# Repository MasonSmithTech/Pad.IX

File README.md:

# Pad.IX, a custom 9 key macropad

this project is a spot where the code, schematics, 3d models, and other files related to the Hack Club Stardance "HackPad" project are located, with my iteration named "Pad.IX" since it has nine keys. 

The Pad.IX is a nine key macro pad with an encoder and OLED screen, with future hopes of implementing VIA for custom keymapping.

## CAD
The case was modeled inside of OnShape (A new tool for me) and renders (as seen above) were created inside of fusion 360. The case features a top piece which holds the switches and pcb, and a bottom piece to protect the electronics, with the two parts being bolted together with M3 bolts and heat press inserts. 
The case was somewhat influenced by the OZO Keyboards Skeleton Keyboard Case, but mainly it is just an interesting looking open shell design that appeared in my brain on the bus home from school!

## PCB
the schematic and PCB are created using KiCad and LOTS of google.

schematic:

PCB:

## Firmware
This hackpad uses QMK firmware for everything.

the rotary encoder changes volume. press to mute
The 9 keys currently act as ma number pad
The OLED is a status display of sorts (mainly says "Pad.IX" tho)
Hopefully VIA support will be added once I actually build the thing irl

Thats pretty much it the firmware was pretty confusing to make so idk what to say

## Bill Of Materials 
    - 9x cherry MX switches
    - 9x DSA Keycaps (not required)
    - 1x 0.91" 128x32 OLED Display
    - 1x Seed XIAO RP2040
    - 1x EC11 Rotary Encoder
    - 1x Custom designed and manufactured pcb
    - 1x 3d printed top housing
    - 1x 3d printed bottom housing
    - 4x M3 heatpress inserts
    - 4x M3x16mm SHCS Bolts
    - 10x 1N4148 DO-35 Diodes

## Software
    - QMK MSYS
    - Fusion 360
    - KiCad 9.0    
    - Onshape
    - Visual Studio Code
    - File Explorer

## Author's Note
Thanks to the people at Hack Club this was an amazing experience! This is my first Hack Club build but I am looking forward to doing so much more in the future!
Also thanks to google cuz this was VERY confusing!

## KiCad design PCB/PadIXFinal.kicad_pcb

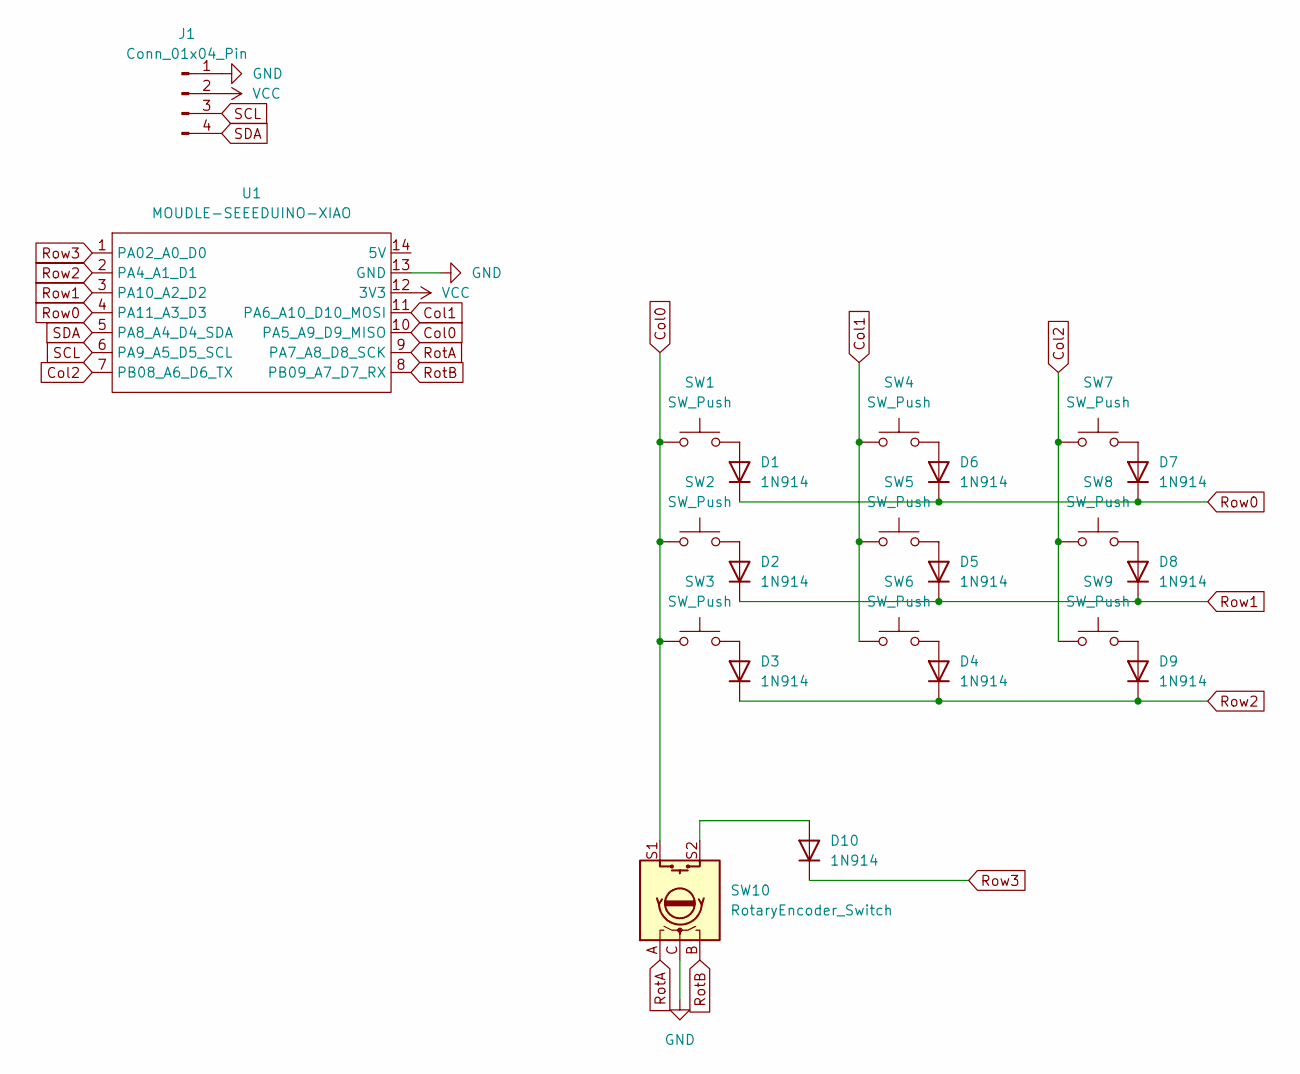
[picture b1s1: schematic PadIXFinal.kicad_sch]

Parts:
D1, D2, D3, D4, D5, D6, D7, D8, D9, D10: 1N914; D_DO-35_SOD27_P7.62mm_Horizontal
J1: Conn_01x04_Pin; PinHeader_1x04_P2.54mm_Vertical
SW1, SW2, SW3, SW4, SW5, SW6, SW7, SW8, SW9: SW_Push; SW_Cherry_MX_1.00u_PCB
SW10: RotaryEncoder_Switch; RotaryEncoder_Alps_EC11E-Switch_Vertical_H20mm
U1: MOUDLE-SEEEDUINO-XIAO; XIAO-Generic-Hybrid-14P-2.54-21X17.8MM

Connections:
Col1: SW4.1, SW5.1, SW6.1, U1.11 (PA6_A10_D10_MOSI)
Col2: SW7.1, SW8.1, SW9.1, U1.7 (PB08_A6_D6_TX)
GND: D10.2 (A), J1.1, SW10.C, SW10.S2, U1.13 (GND)
unnamed: D1.2 (A), SW1.2
unnamed: D2.2 (A), SW2.2
unnamed: D3.2 (A), SW3.2
unnamed: D4.2 (A), SW6.2
unnamed: D5.2 (A), SW5.2
unnamed: D6.2 (A), SW4.2
unnamed: D7.2 (A), SW7.2
unnamed: D8.2 (A), SW8.2
unnamed: D9.2 (A), SW9.2
RotA: SW10.A, U1.9 (PA7_A8_D8_SCK)
RotB: SW10.B, U1.8 (PB09_A7_D7_RX)
Row0: D1.1 (K), D6.1 (K), D7.1 (K), U1.4 (PA11_A3_D3)
Row1: D2.1 (K), D5.1 (K), D8.1 (K), U1.3 (PA10_A2_D2)
Row2: D3.1 (K), D4.1 (K), D9.1 (K), U1.2 (PA4_A1_D1)
SCL: J1.3, U1.6 (PA9_A5_D5_SCL)
SDA: J1.4, U1.5 (PA8_A4_D4_SDA)
VCC: J1.2, U1.12 (3V3)

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
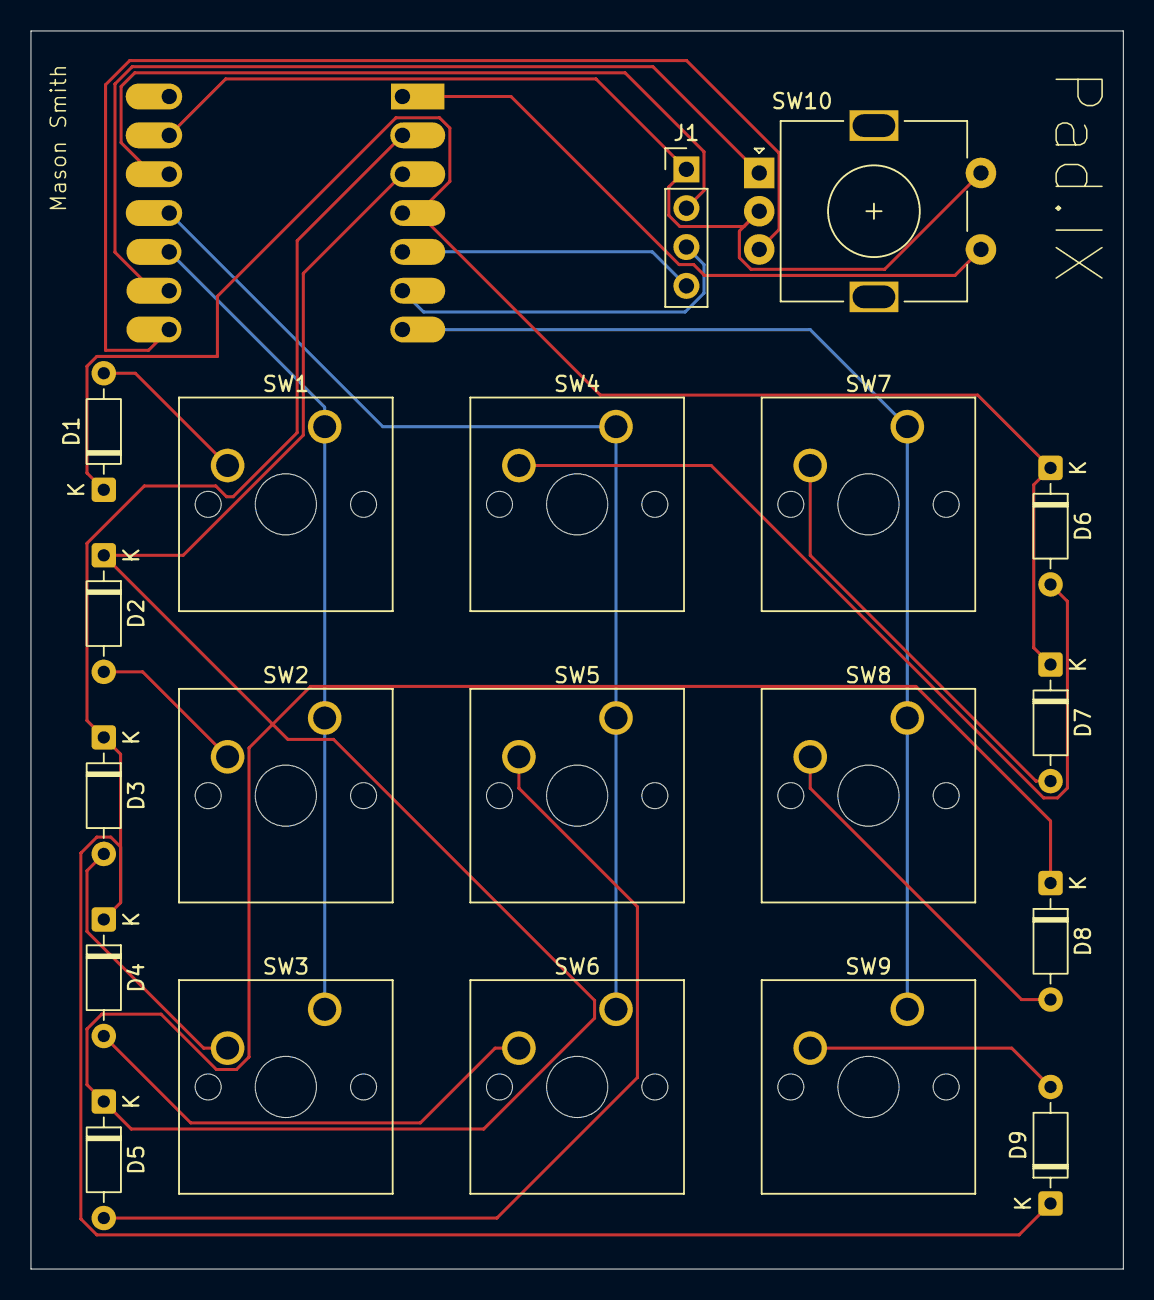
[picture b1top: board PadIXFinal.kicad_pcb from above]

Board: 2 copper layers, 71.4 x 81.0 mm, 21 parts (1 on the bottom side), 22 nets.

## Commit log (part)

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2026-06-14 Created Chud README
2026-06-15 fleshed out readme
2026-06-15 Made a MIT License
